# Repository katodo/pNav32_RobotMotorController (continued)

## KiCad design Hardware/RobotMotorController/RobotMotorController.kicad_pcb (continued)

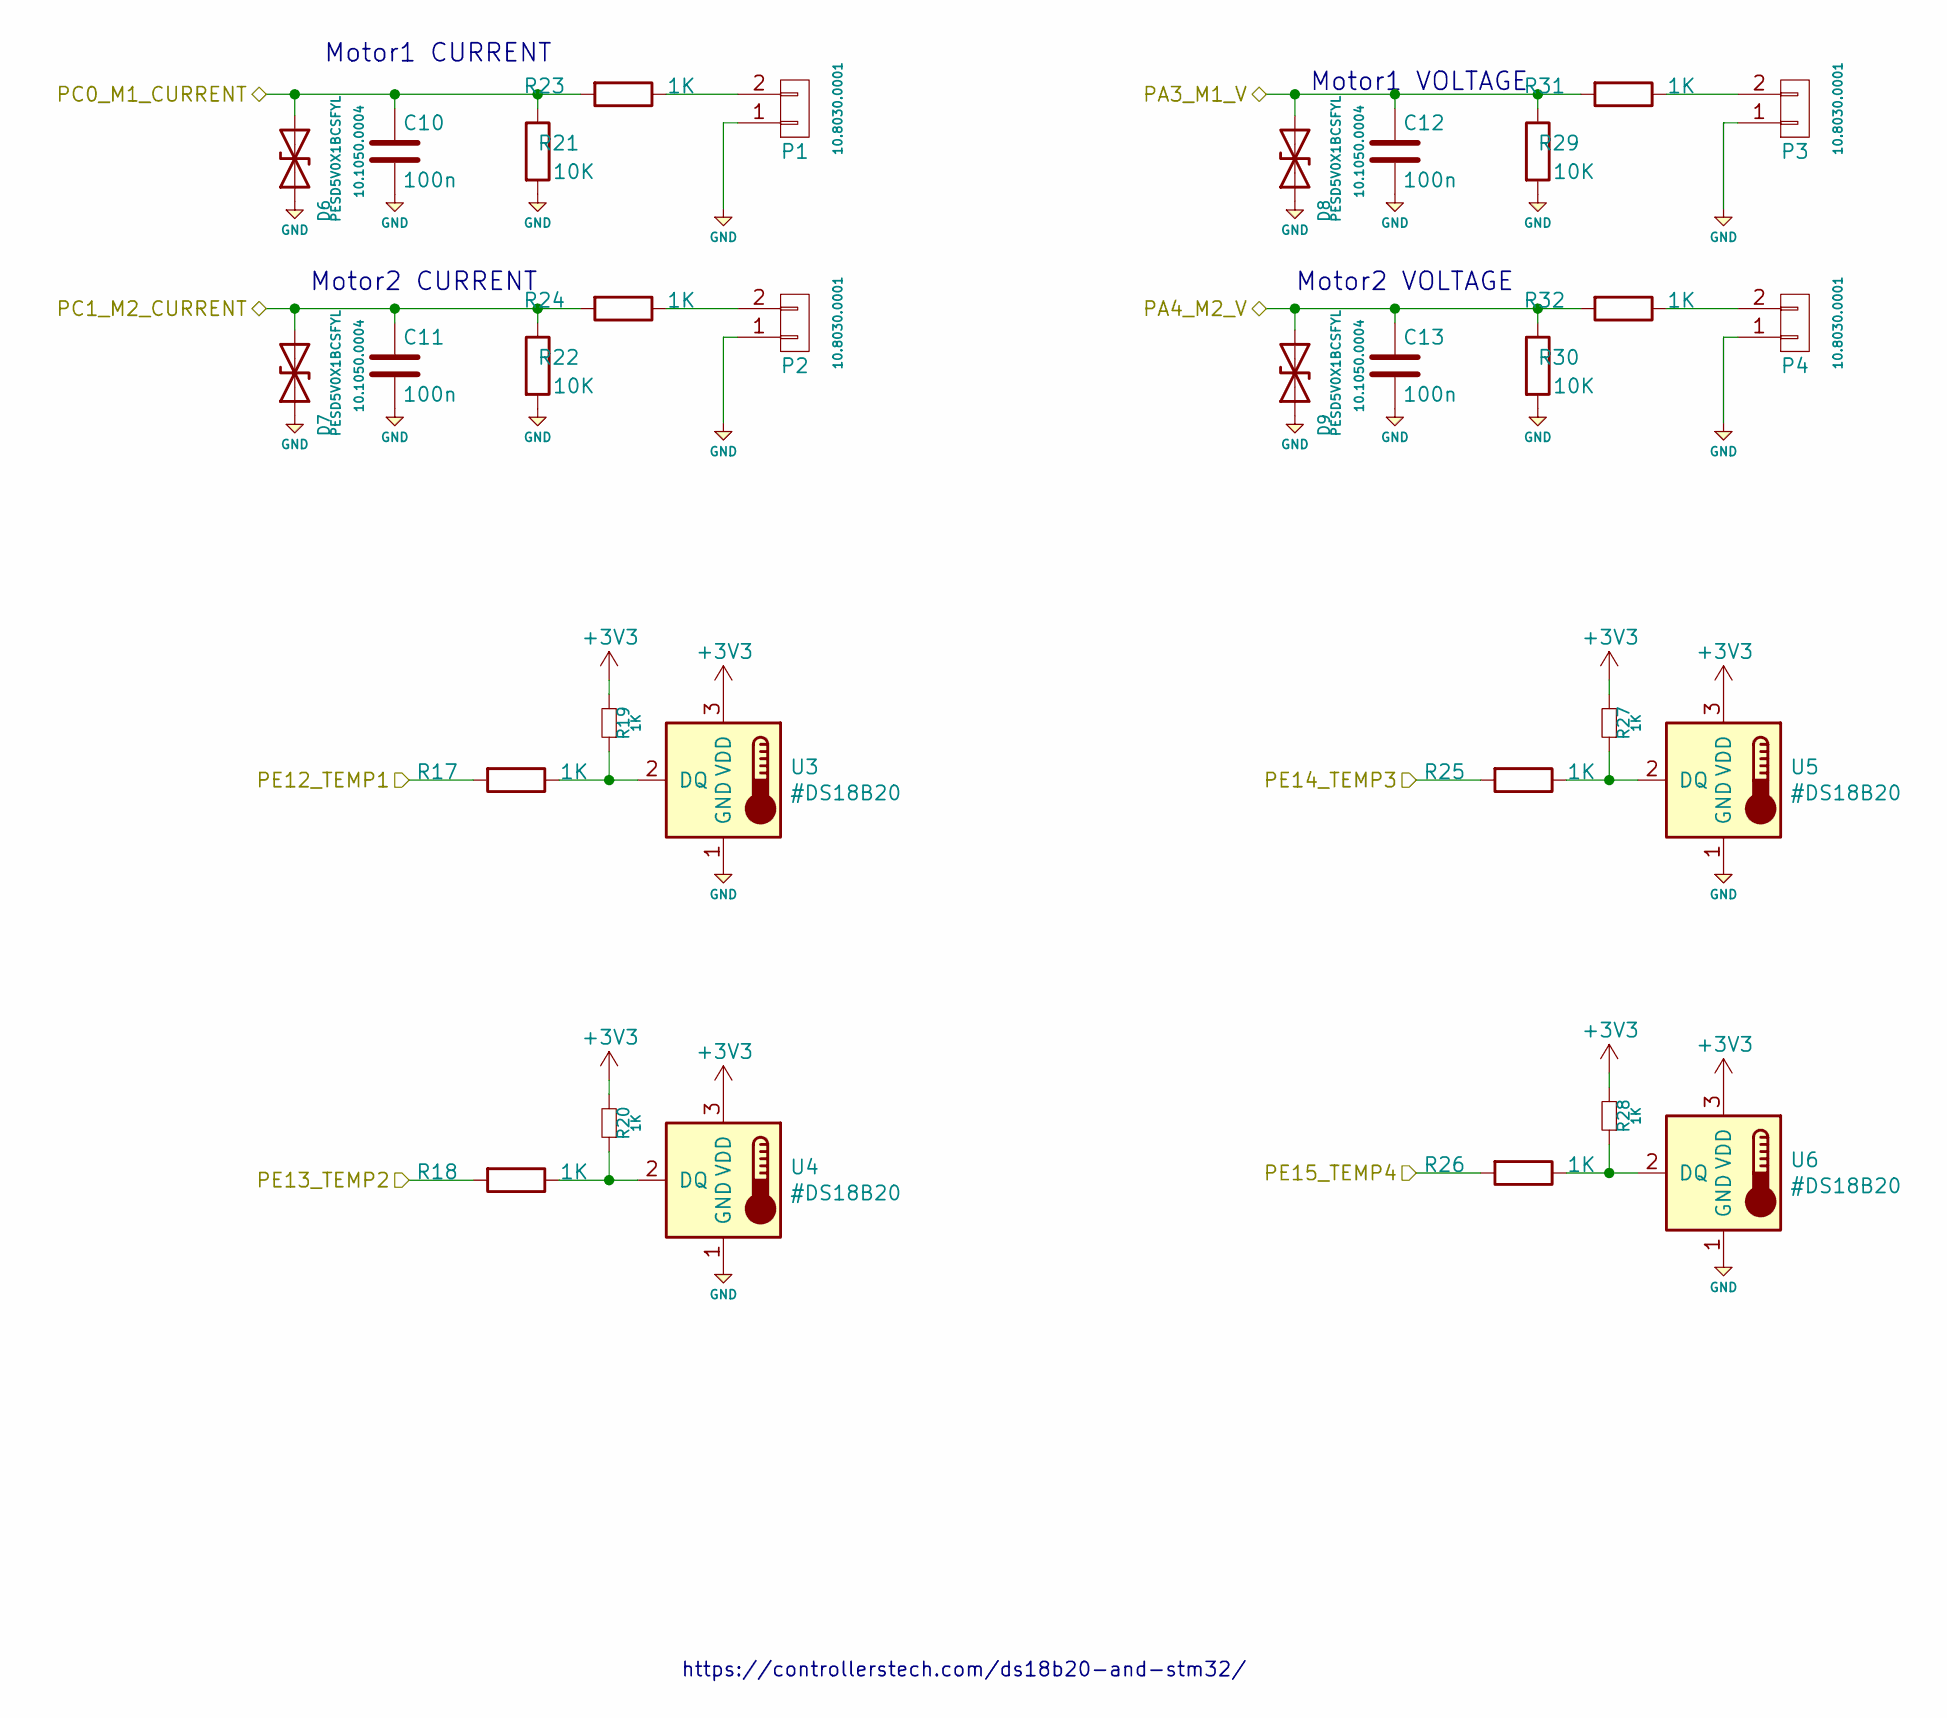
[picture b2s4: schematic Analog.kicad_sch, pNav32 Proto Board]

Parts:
C10, C11, C12, C13: 100n; C_0603_1608Metric; LCSC C14663
D6, D7, D8, D9: PESD5V0X1BCSFYL; D_0603_1608Metric; LCSC C2443412
P1, P2, P3, P4: Molex_KK-254_AE-6410-02A_1x02_P2.54mm_Vertical
R17, R18, R23, R24, R25, R26, R31, R32: 1K; R_0603_1608Metric; LCSC C21190
R19, R20, R27, R28: 1K; R_0603_1608Metric; MPN CRCW06031K00FKEA; FARNELL 2122366
R21, R22, R29, R30: 10K; R_0603_1608Metric; LCSC C25804
U3, U4, U5, U6: #DS18B20; TO-92_Inline; MPN DS18B20

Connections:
+3V3: R19.2, R20.2, R27.2, R28.2, U3.3 (VDD), U4.3 (VDD), U5.3 (VDD), U6.3 (VDD); also elsewhere on the board
unnamed: P1.2, R23.1
unnamed: P2.2, R24.1
unnamed: P3.2, R31.1
unnamed: P4.2, R32.1
unnamed: R17.1, R19.1, U3.2 (DQ)
unnamed: R18.1, R20.1, U4.2 (DQ)
unnamed: R25.1, R27.1, U5.2 (DQ)
unnamed: R26.1, R28.1, U6.2 (DQ)
PA3_M1_V: C12.1, D8.2 (A2), R29.1, R31.2; also elsewhere on the board
PA4_M2_V: C13.1, D9.2 (A2), R30.1, R32.2; also elsewhere on the board
PC0_M1_CURRENT: C10.1, D6.2 (A2), R21.1, R23.2; also elsewhere on the board
PC1_M2_CURRENT: C11.1, D7.2 (A2), R22.1, R24.2; also elsewhere on the board
PE12_TEMP1: R17.2; also elsewhere on the board
PE13_TEMP2: R18.2; also elsewhere on the board
PE14_TEMP3: R25.2; also elsewhere on the board
PE15_TEMP4: R26.2; also elsewhere on the board

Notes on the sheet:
Motor1 CURRENT
Motor1 VOLTAGE
Motor2 VOLTAGE
https://controllerstech.com/ds18b20-and-stm32/
Motor2 CURRENT

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
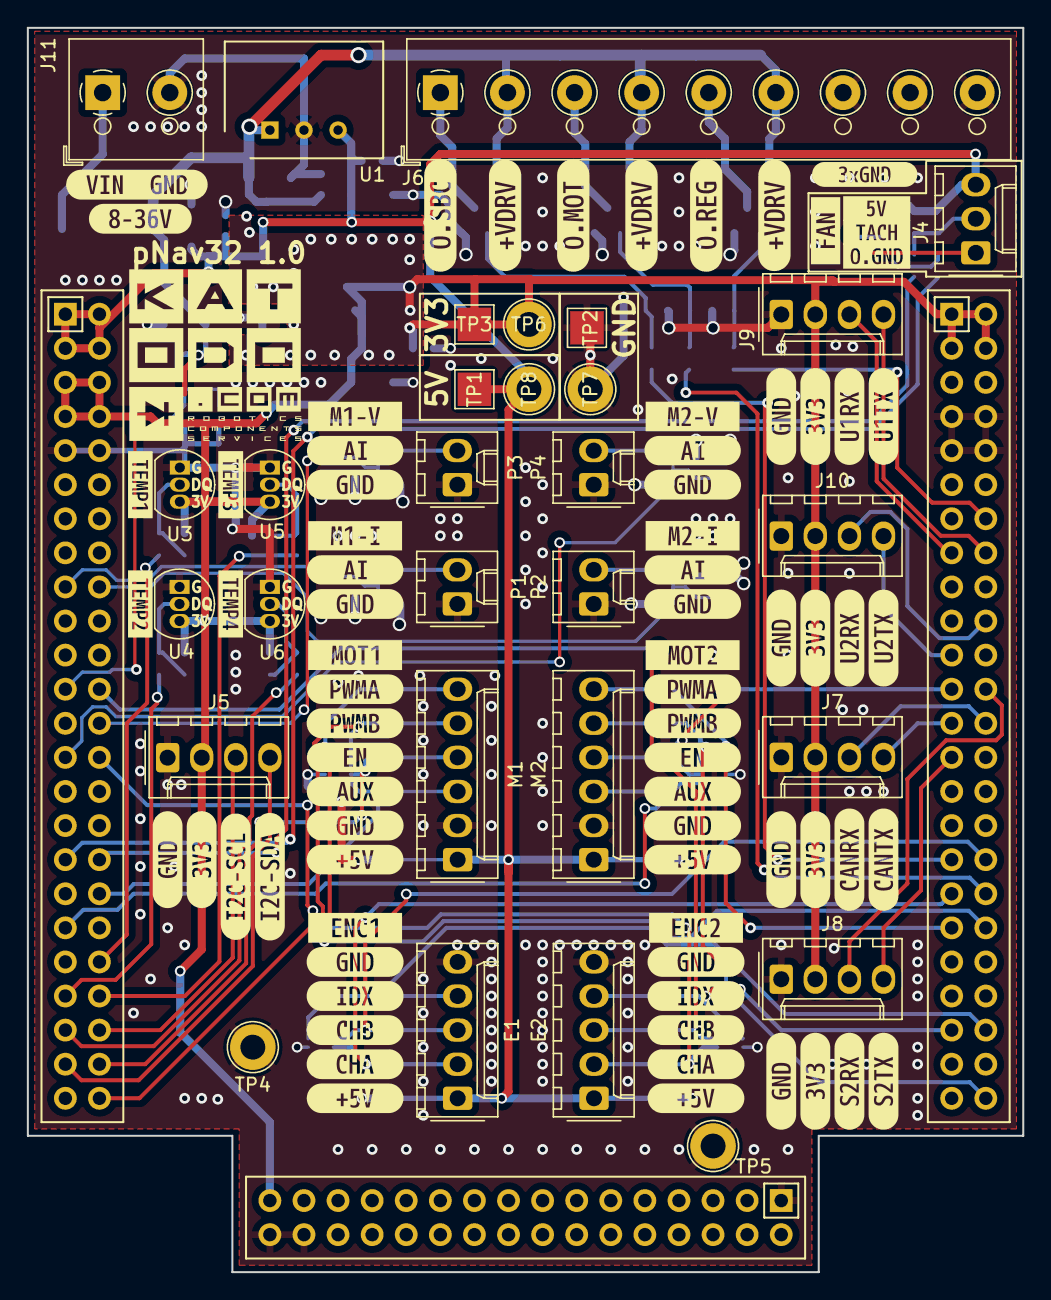
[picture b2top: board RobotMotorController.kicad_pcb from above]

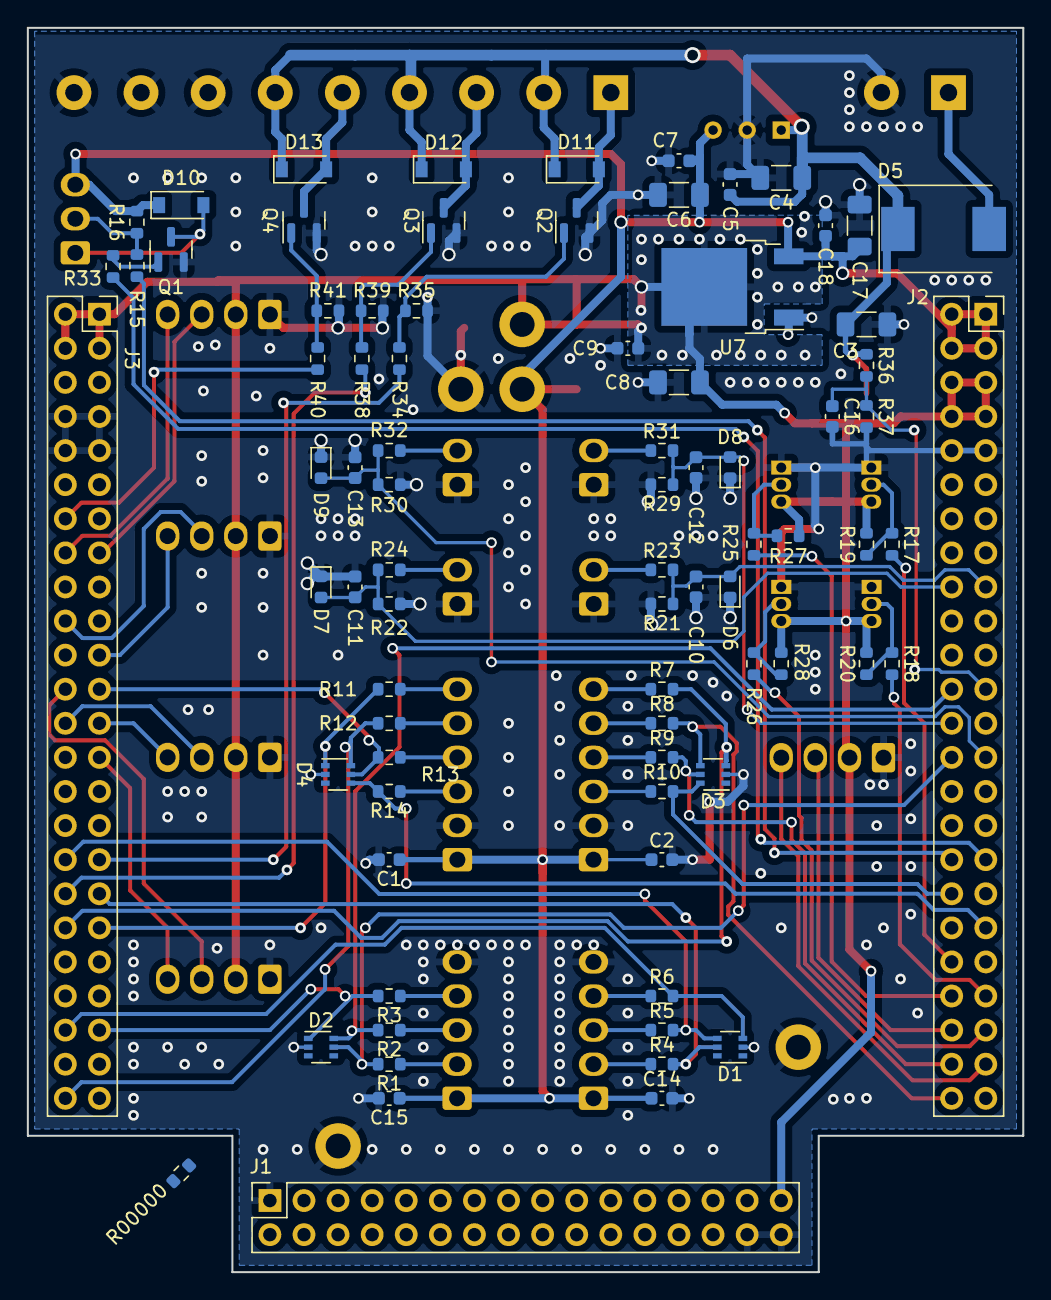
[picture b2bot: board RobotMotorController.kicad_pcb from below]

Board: 2 copper layers, 74.2 x 92.7 mm, 185 parts (81 on the bottom side), 74 nets.

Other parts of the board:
kibuzzard-63AACC29: G***; kibuzzard-63AACC29
kibuzzard-63AACC33: G***; kibuzzard-63AACC33
kibuzzard-63AACC58: G***; kibuzzard-63AACC58
kibuzzard-63AAD1E2: G***; kibuzzard-63AAD1E2
kibuzzard-63AAD7A3: G***; kibuzzard-63AAD7A3
kibuzzard-63AAD7D2: G***; kibuzzard-63AAD7D2
kibuzzard-63AAD7EB: G***; kibuzzard-63AAD7EB
kibuzzard-63AAD7FB: G***; kibuzzard-63AAD7FB
kibuzzard-63AAD203: G***; kibuzzard-63AAD203
kibuzzard-63AAD219: G***; kibuzzard-63AAD219
kibuzzard-63AAD233: G***; kibuzzard-63AAD233
kibuzzard-63AAD280: G***; kibuzzard-63AAD280
kibuzzard-63AAD289: G***; kibuzzard-63AAD289
kibuzzard-63AAD294: G***; kibuzzard-63AAD294
kibuzzard-63AB02C8: G***; kibuzzard-63AB02C8
kibuzzard-6394D4E3, kibuzzard-6394D4E3#2, kibuzzard-6394D4E3#3, kibuzzard-6394D4E3#4, kibuzzard-6394D4E3#5: G***; kibuzzard-6394D4E3
kibuzzard-6394D4F3, kibuzzard-6394D4F3#2, kibuzzard-6394D4F3#3, kibuzzard-6394D4F3#4, kibuzzard-6394D4F3#5: G***; kibuzzard-6394D4F3
kibuzzard-6394D8B5: G***; kibuzzard-6394D8B5
kibuzzard-6394D8C1: G***; kibuzzard-6394D8C1
kibuzzard-6394D9EA: G***; kibuzzard-6394D9EA
kibuzzard-6394D50C: G***; kibuzzard-6394D50C
kibuzzard-6394D52A: G***; kibuzzard-6394D52A
kibuzzard-6394D54D: G***; kibuzzard-6394D54D
kibuzzard-6394D57A: G***; kibuzzard-6394D57A
kibuzzard-6394D504: G***; kibuzzard-6394D504
kibuzzard-6394D524: G***; kibuzzard-6394D524
kibuzzard-6394D557: G***; kibuzzard-6394D557
kibuzzard-6394D572: G***; kibuzzard-6394D572
kibuzzard-6395EE3C: G***; kibuzzard-6395EE3C
kibuzzard-63934B9D, kibuzzard-63934B9D#2: G***; kibuzzard-63934B9D
kibuzzard-63934B92, kibuzzard-63934B92#2: G***; kibuzzard-63934B92
kibuzzard-63934BBB: G***; kibuzzard-63934BBB
kibuzzard-63934BC4: G***; kibuzzard-63934BC4
kibuzzard-63934BD1, kibuzzard-63934BD1#2: G***; kibuzzard-63934BD1
kibuzzard-63934BD9, kibuzzard-63934BD9#2: G***; kibuzzard-63934BD9
kibuzzard-63934BF1: G***; kibuzzard-63934BF1
kibuzzard-63934BF7: G***; kibuzzard-63934BF7
kibuzzard-639345B8: G***; kibuzzard-639345B8
kibuzzard-6393426E, kibuzzard-6393426E#2: G***; kibuzzard-6393426E
kibuzzard-6393456C, kibuzzard-6393456C#2: G***; kibuzzard-6393456C
kibuzzard-6393459E: G***; kibuzzard-6393459E
kibuzzard-6393473F, kibuzzard-6393473F#2: G***; kibuzzard-6393473F
kibuzzard-63934268, kibuzzard-63934268#2: G***; kibuzzard-63934268
kibuzzard-63934273, kibuzzard-63934273#2, kibuzzard-63934273#3, kibuzzard-63934273#4: G***; kibuzzard-63934273
kibuzzard-63934574, kibuzzard-63934574#2: G***; kibuzzard-63934574
kibuzzard-63934711: G***; kibuzzard-63934711
kibuzzard-63934735, kibuzzard-63934735#2: G***; kibuzzard-63934735
kibuzzard-63934749, kibuzzard-63934749#2: G***; kibuzzard-63934749
kibuzzard-63934750, kibuzzard-63934750#2: G***; kibuzzard-63934750
kibuzzard-63934760, kibuzzard-63934760#2: G***; kibuzzard-63934760
kibuzzard-63934774: G***; kibuzzard-63934774

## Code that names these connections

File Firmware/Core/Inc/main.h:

/* USER CODE BEGIN Header */
/**
  ******************************************************************************
  * @file           : main.h
  * @brief          : Header for main.c file.
  *                   This file contains the common defines of the application.
  ******************************************************************************
  * @attention
  *
  * Copyright (c) 2022 STMicroelectronics.
  * All rights reserved.
  *
  * This software is licensed under terms that can be found in the LICENSE file
  * in the root directory of this software component.
  * If no LICENSE file comes with this software, it is provided AS-IS.
  *
  ******************************************************************************
  */
/* USER CODE END Header */

/* Define to prevent recursive inclusion -------------------------------------*/
#ifndef __MAIN_H
#define __MAIN_H

#ifdef __cplusplus
extern "C" {
#endif

/* Includes ------------------------------------------------------------------*/
#include "stm32f4xx_hal.h"

/* Private includes ----------------------------------------------------------*/
/* USER CODE BEGIN Includes */

/* USER CODE END Includes */

/* Exported types ------------------------------------------------------------*/
/* USER CODE BEGIN ET */

/* USER CODE END ET */

/* Exported constants --------------------------------------------------------*/
/* USER CODE BEGIN EC */

/* USER CODE END EC */

/* Exported macro ------------------------------------------------------------*/
/* USER CODE BEGIN EM */

/* USER CODE END EM */

/* Exported functions prototypes ---------------------------------------------*/
void Error_Handler(void);

/* USER CODE BEGIN EFP */

/* USER CODE END EFP */

/* Private defines -----------------------------------------------------------*/
#define I_KEY1_Pin GPIO_PIN_3
#define I_KEY1_GPIO_Port GPIOE
#define I_KEY0_Pin GPIO_PIN_4
#define I_KEY0_GPIO_Port GPIOE
#define PC0_M1_CURRENT_Pin GPIO_PIN_0
#define PC0_M1_CURRENT_GPIO_Port GPIOC
#define PC1_M2_CURRENT_Pin GPIO_PIN_1
#define PC1_M2_CURRENT_GPIO_Port GPIOC
#define PA0_MAIN_SUPPLY_Pin GPIO_PIN_0
#define PA0_MAIN_SUPPLY_GPIO_Port GPIOA
#define TIM_ENC2_B_Pin GPIO_PIN_1
#define TIM_ENC2_B_GPIO_Port GPIOA
#define PA3_M1_V_Pin GPIO_PIN_3
#define PA3_M1_V_GPIO_Port GPIOA
#define PA4_M2_V_Pin GPIO_PIN_4
#define PA4_M2_V_GPIO_Port GPIOA
#define TIM_ENC2_A_Pin GPIO_PIN_5
#define TIM_ENC2_A_GPIO_Port GPIOA
#define O_LED_D2_Pin GPIO_PIN_6
#define O_LED_D2_GPIO_Port GPIOA
#define O_LED_D3_Pin GPIO_PIN_7
#define O_LED_D3_GPIO_Port GPIOA
#define TIM_FAN_PWM_Pin GPIO_PIN_0
#define TIM_FAN_PWM_GPIO_Port GPIOB
#define TIM_FAN_INDEX_Pin GPIO_PIN_1
#define TIM_FAN_INDEX_GPIO_Port GPIOB
#define PE8_MOT1_AUX_Pin GPIO_PIN_8
#define PE8_MOT1_AUX_GPIO_Port GPIOE
#define PE9_MOT2_AUX_Pin GPIO_PIN_9
#define PE9_MOT2_AUX_GPIO_Port GPIOE
#define PE12_TEMP1_Pin GPIO_PIN_12
#define PE12_TEMP1_GPIO_Port GPIOE
#define PE13_TEMP2_Pin GPIO_PIN_13
#define PE13_TEMP2_GPIO_Port GPIOE
#define PE14_TEMP3_Pin GPIO_PIN_14
#define PE14_TEMP3_GPIO_Port GPIOE
#define PE15_TEMP4_Pin GPIO_PIN_15
#define PE15_TEMP4_GPIO_Port GPIOE
#define I2C_SCL_Pin GPIO_PIN_10
#define I2C_SCL_GPIO_Port GPIOB
#define I2C_SDA_Pin GPIO_PIN_11
#define I2C_SDA_GPIO_Port GPIOB
#define PB12_MOT1_EN_Pin GPIO_PIN_12
#define PB12_MOT1_EN_GPIO_Port GPIOB
#define PB14_TIM8_MOT1_N_Pin GPIO_PIN_14
#define PB14_TIM8_MOT1_N_GPIO_Port GPIOB
#define PB15_TIM8_MOT2_N_Pin GPIO_PIN_15
#define PB15_TIM8_MOT2_N_GPIO_Port GPIOB
#define PD11_EXTI11_E1_IDX_Pin GPIO_PIN_11
#define PD11_EXTI11_E1_IDX_GPIO_Port GPIOD
#define PD12_EXTI12_E2_IDX_Pin GPIO_PIN_12
#define PD12_EXTI12_E2_IDX_GPIO_Port GPIOD
#define ENC2_A_SPEED_Pin GPIO_PIN_13
#define ENC2_A_SPEED_GPIO_Port GPIOD
#define ENC1_A_SPEED_Pin GPIO_PIN_6
#define ENC1_A_SPEED_GPIO_Port GPIOC
#define PC7_TIM8_MOT1_P_Pin GPIO_PIN_7
#define PC7_TIM8_MOT1_P_GPIO_Port GPIOC
#define PC8_TIM8_MOT2_P_Pin GPIO_PIN_8
#define PC8_TIM8_MOT2_P_GPIO_Port GPIOC
#define O_PWR_SBC_EN_Pin GPIO_PIN_9
#define O_PWR_SBC_EN_GPIO_Port GPIOC
#define TIM_ENC1_A_Pin GPIO_PIN_8
#define TIM_ENC1_A_GPIO_Port GPIOA
#define TIM_ENC1_B_Pin GPIO_PIN_9
#define TIM_ENC1_B_GPIO_Port GPIOA
#define O_PWR_MOT_EN_Pin GPIO_PIN_10
#define O_PWR_MOT_EN_GPIO_Port GPIOA
#define O_SPI_CS2_Pin GPIO_PIN_10
#define O_SPI_CS2_GPIO_Port GPIOC
#define O_SPI_CS1_Pin GPIO_PIN_11
#define O_SPI_CS1_GPIO_Port GPIOC
#define SER2_TX_Pin GPIO_PIN_12
#define SER2_TX_GPIO_Port GPIOC
#define SER2_RX_Pin GPIO_PIN_2
#define SER2_RX_GPIO_Port GPIOD
#define PD3_MOT2_EN_Pin GPIO_PIN_3
#define PD3_MOT2_EN_GPIO_Port GPIOD
#define O_PWR_REG_EN_Pin GPIO_PIN_8
#define O_PWR_REG_EN_GPIO_Port GPIOB
#define TIM_AUX2_PWM_Pin GPIO_PIN_9
#define TIM_AUX2_PWM_GPIO_Port GPIOB

/* USER CODE BEGIN Private defines */

/* USER CODE END Private defines */

#ifdef __cplusplus
}
#endif

#endif /* __MAIN_H */

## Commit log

2022-10-20 Initial semi-empty project, a basic test code with 2 freeRTOS BlinkLed
2022-10-20 Updated to new git project location
2022-10-21 completed the configuration of the peripherals.
2022-10-24 Minor Changes
2022-10-25 First Micro-Ros implementation
2022-10-27 test with publishing o different messages... FAIL...
2022-10-27 Publish messages test.
2022-11-02 Test...
2022-11-27 Solved problem on Battery message publishing
2022-12-29 Hardware release 1.0 produced by JLCPCB
2022-12-29 changed 1N4148 JLCPCB code and value of R1 and R00000 resistor.
2023-01-07 hBridge3620 V1.0
2023-01-19 varius improvement
2023-01-25 Start configuration ADC1 and ADC3
2023-01-26 ADC init completed
2025-01-06 General update, first encoder implementation
2025-01-12 first test of encoder implementation with ROS2
2025-01-23 lettura durata impulso inizia a funzionare ma con troppo errore
2025-01-23 Aggiornamento Kicad
2025-01-27 Calcolo di impulse_time resettando ogni volta il contatore
